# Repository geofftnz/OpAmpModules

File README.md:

# Simple OpAmp Project Boards
by @geofftnz

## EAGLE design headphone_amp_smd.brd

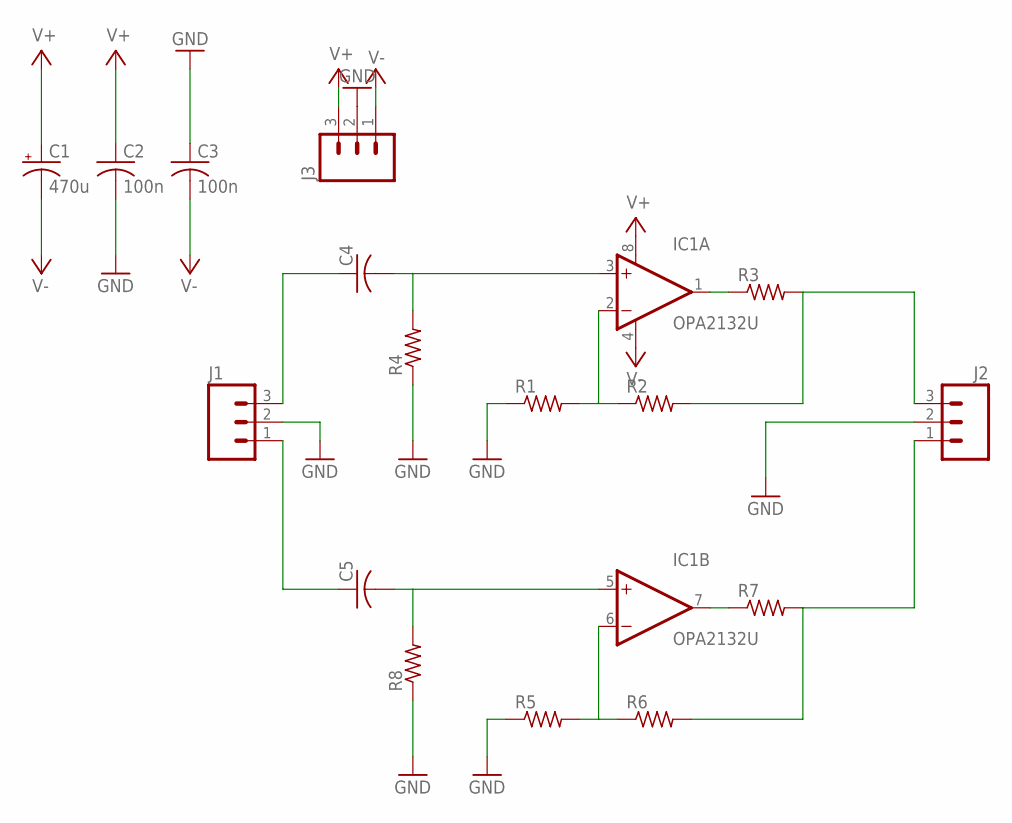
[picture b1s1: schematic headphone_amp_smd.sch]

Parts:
C1: 470u; E5-10,5
C2, C3: 100n; C0805K
C4, C5: C-US025_050-035X075; C025_050-035X075
IC1: OPA2132U; SO08
J1, J2, J3: M03PTH; 1X03
R1, R2, R3, R4, R5, R6, R7, R8: R-US_R1206; R1206

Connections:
GND: C2.2, C3.1, J1.2, J2.2, J3.2, R1.1, R4.1, R5.1, R8.1
unnamed: IC1.1 (OUT), R3.1
unnamed: J2.3, R2.2, R3.2
unnamed: IC1.2 (-IN), R1.2, R2.1
unnamed: C4.1, J1.3
unnamed: C4.2, IC1.3 (+IN), R4.2
unnamed: IC1.7 (OUT), R7.1
unnamed: J2.1, R6.2, R7.2
unnamed: IC1.6 (-IN), R5.2, R6.1
unnamed: C5.2, IC1.5 (+IN), R8.2
unnamed: C5.1, J1.1
V+: C1.+, C2.1, IC1.8 (V+), J3.3
V-: C1.-, C3.2, IC1.4 (V-), J3.1

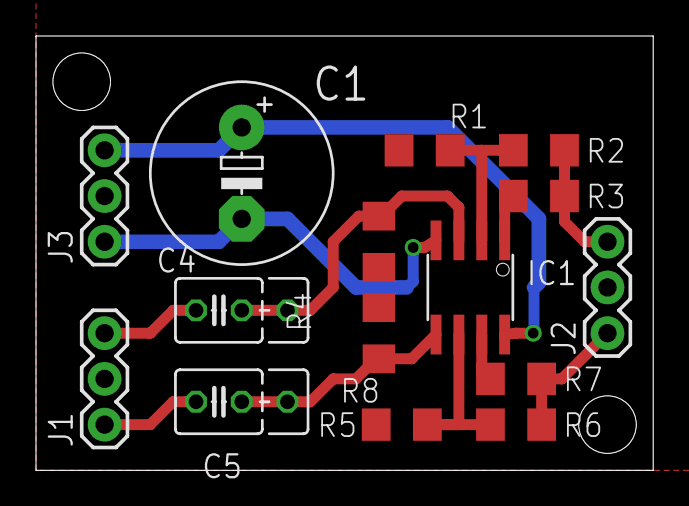
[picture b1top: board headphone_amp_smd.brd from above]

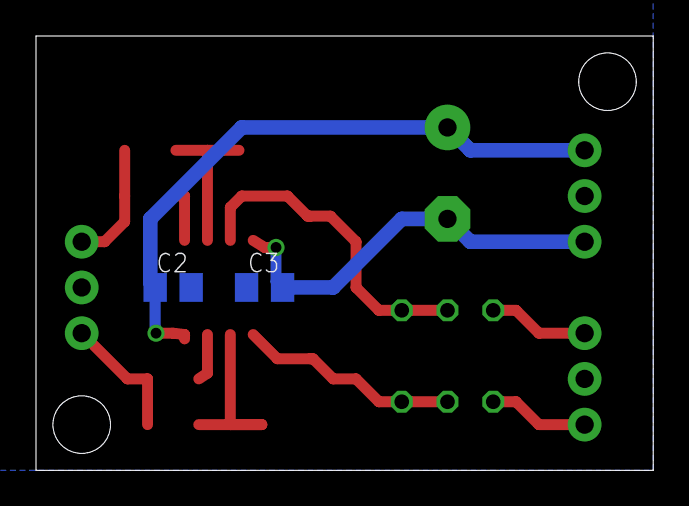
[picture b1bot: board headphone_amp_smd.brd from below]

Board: 2 copper layers, 34.3 x 24.1 mm, 17 parts (2 on the bottom side), 13 nets.

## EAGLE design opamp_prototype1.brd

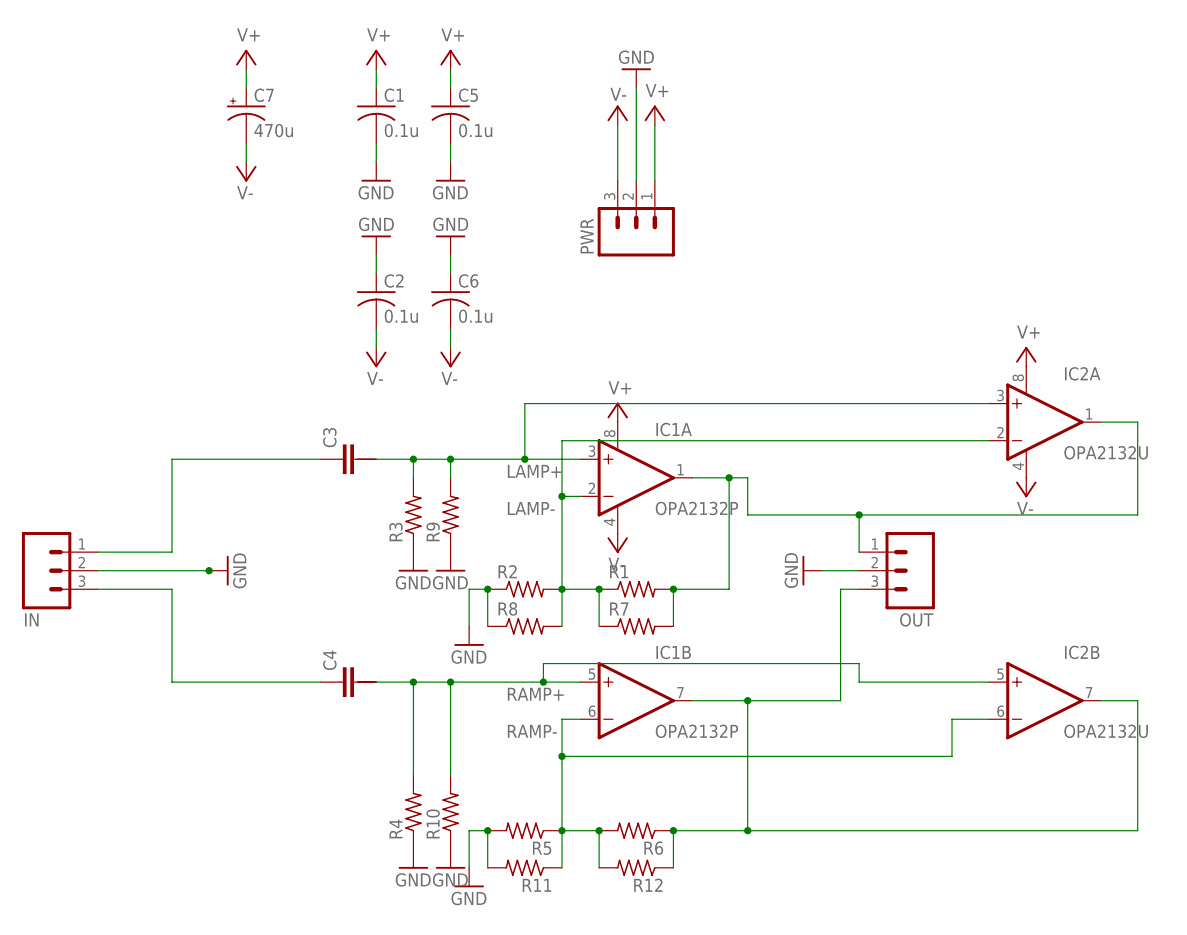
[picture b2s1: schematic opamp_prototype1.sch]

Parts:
C1, C2, C5, C6: 0.1u; C0805K
C3, C4: C-2.5-5/6; C2.5/5-6
C7: 470u; CPOL-RADIAL-1000UF-25V
IC1: OPA2132P; DIL08
IC2: OPA2132U; SO08
IN: M03PTH; 1X03
OUT: M03PTH; 1X03
PWR: M03PTH; 1X03
R1, R2, R3, R4, R5, R6: R-US_0207/10; 0207/10
R7, R8, R9, R10, R11, R12: R-US_R1206; R1206

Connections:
GND: C1.2, C2.1, C5.2, C6.1, IN.2, OUT.2, PWR.2, R2.1, R3.1, R4.1, R5.2, R8.1, R9.1, R10.1, R11.2
IN_L: C3.1, IN.1
LAMP+: C3.2, IC1.3 (+IN), IC2.3 (+IN), R3.2, R9.2
LAMP-: IC1.2 (-IN), IC2.2 (-IN), R1.1, R2.2, R7.1, R8.2
unnamed: C4.1, IN.3
OUT_L: IC1.1 (OUT), IC2.1 (OUT), OUT.1, R1.2, R7.2
OUT_R: IC1.7 (OUT), IC2.7 (OUT), OUT.3, R6.1, R12.1
RAMP+: C4.2, IC1.5 (+IN), IC2.5 (+IN), R4.2, R10.2
RAMP-: IC1.6 (-IN), IC2.6 (-IN), R5.1, R6.2, R11.1, R12.2
V+: C1.1, C5.1, C7.+, IC1.8 (V+), IC2.8 (V+), PWR.1
V-: C2.2, C6.2, C7.-, IC1.4 (V-), IC2.4 (V-), PWR.3

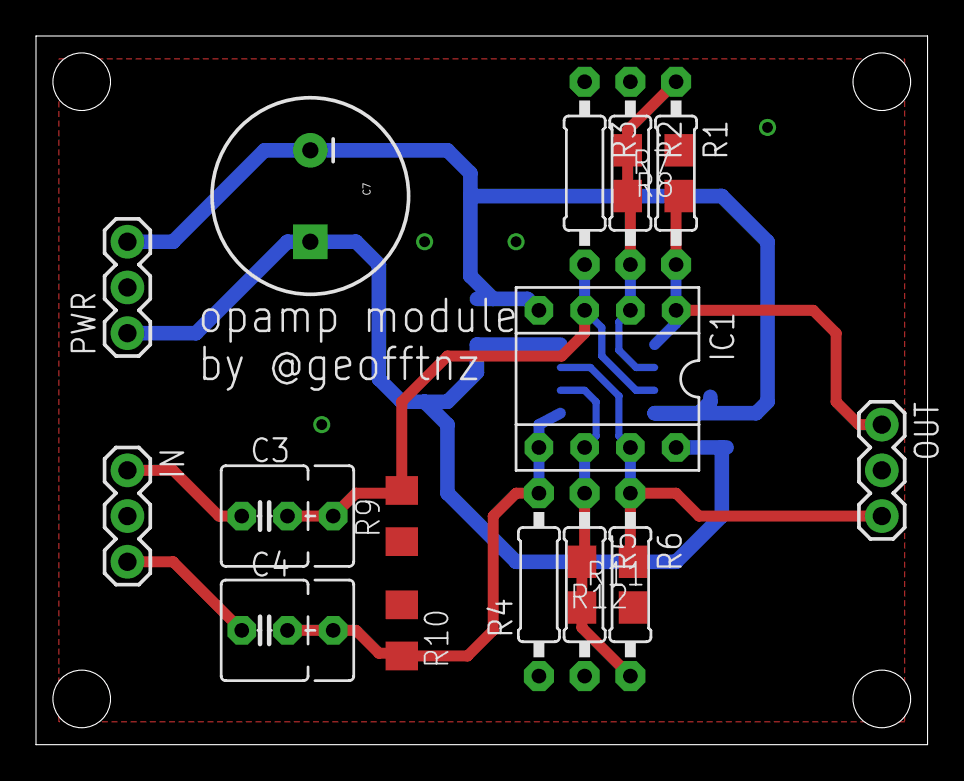
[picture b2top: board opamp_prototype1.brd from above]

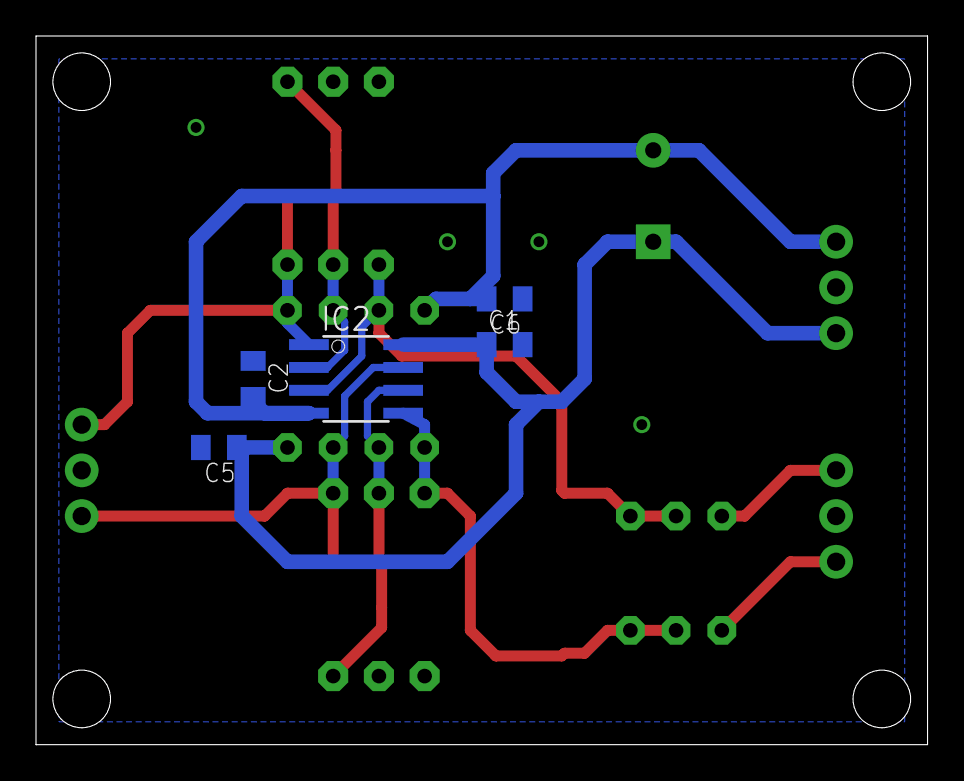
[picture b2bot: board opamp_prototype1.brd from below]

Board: 2 copper layers, 49.5 x 39.4 mm, 24 parts (5 on the bottom side), 11 nets.

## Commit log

2016-03-21 project setup
2016-03-21 basic headphone amp
2016-03-21 added text, moved gnd via
2016-03-21 Added SMD resistor option
2016-03-21 tidy up
2016-03-21 start of possible power board
2016-03-22 adding small mostly-SMD headphone amp

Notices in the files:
parts and their libraries:
SparkFun-Connectors: Licensing: Creative Commons ShareAlike 4.0 International - https://creativecommons.org/licenses/by-sa/4.0
